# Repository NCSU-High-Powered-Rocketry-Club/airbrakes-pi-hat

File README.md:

# airbrakes-pi-hat

Custom made Pi hat, named "Airbender", for use in Airbrakes

This repository contains the KiCad project files for a Raspberry Pi hat. This Pi hat is meant to control
airbrakes (see the [airbrakes repository](https://github.com/NCSU-High-Powered-Rocketry-Club/AirbrakesV2) for more details on the airbrakes system).

## Features

- Supports from 7V to 20V input voltage, with a maximum amperage of 10A.
- Variable output voltage for the servo power rail (6V to 13V), while simultaneously powering the Pi at 5V.
- Current and voltage sensing for the entire board, which allows measurement of servo load transients.
- Reverse polarity detection and protection on the input power rail
- Reverse polarity detection and protection for the servo cable. Plugging in the cable backwards now will not fry the Raspberry Pi.
- 7 LEDs for monitoring and detecting the health of the board and its interface with the Raspberry Pi.
- Solder jumper pad to select using a servo via PWM or communicate with the servo via UART
- P-MOSFET to disable power to the servo rail when not in use
- Software controlled buzzer for audible alerts

The repository includes schematic symbols, PCB footprints, 3D models, and all board files necessary to review, edit and manufacture the module.

---

## Quick Start — open the project

1. Install KiCad (see [Install and Setup](#install-and-setup) below).
2. Clone the repository:
```bash
git clone https://github.com/NCSU-High-Powered-Rocketry-Club/airbrakes-pi-hat.git && cd airbrakes-pi-hat
```

---

## Install and Setup

First, install KiCad from [kicad.org](https://kicad.org/download/). We recommend using the latest stable release of KiCad for new designs.

### After installation
- Open the `pcb-hat.kicad_pro` project. KiCad will use the `sym-lib-table` and `fp-lib-table` files included here if you open the board/schematic from this checkout.
- If KiCad shows missing library warnings, update the Project Library Tables or use the library manager to add the project's `sym-lib-table` and `fp-lib-table`.

---

## Repository structure

Root-level description (key files/folders):

- `milled_ab_pi_hat/` — folder containing CNC milling files for in-house fabrication at the ECE Makerspace
- `pcb-hat/` — folder which contains the project files for the SMD version of the Pi hat (This is what we order from JLCPCB!)
- `pcb-hat.kicad_sch` — schematic
- `pcb-hat.kicad_pcb` — PCB layout
- `pcb-hat.kicad_pro` — KiCad project file that links schematics, board and library tables
- `sym-lib-table` — project symbol library table that makes project-local symbols available to Eeschema
- `fp-lib-table` — project footprint library table that makes project-local footprints available
- `3dmodels/` — 3D STEP/WRL models used with footprints
- `symbols/` — human-editable symbol libraries (e.g., `connectors.kicad_sym`, `sensors.kicad_sym`)
- `footprints/` — footprint libraries as `.pretty` directories

---

## Library handling

We keep the project-specific libraries inside the repository so that board designs are reproducible and self-contained.

### Symbols
- New symbols are added to the project's `symbols` directory and are registered in the project's `sym-lib-table`.

### Footprints
- Footprints live inside `.pretty` folders in `footprints/`. Add footprints via the footprint editor and store them in an appropriate `footprints/<libname>.pretty` folder.

### 3D models
- 3D models are stored in `3dmodels/` and referenced by footprint model paths. Keep STEP files with good orientation and scale (KiCad's default is mm). We typically download the .step file from the manufacturer's website.
- If you add a footprint that references a 3D model, commit both the footprint in `footprints/` and the 3D model to `3dmodels/`.

---

## Good Practices & Design Rules

- Keep schematic symbols generic and footprints specific: do not hardcode assembly-side changes into symbols.
- Look at the existing schematic to see how we do things and try to be consistent.
- Save new libraries to the project-local tables (not global) to keep designs reproducible.
- Keep PCB footprints accurate — use accurate courtyard, 3D models, and update packaging information.
- Validate with DRC (PCB Editor > Inspect > Design Rules Checker) and ERC (Eeschema > Tools > ERC) before committing changes.
- When collaborating, include notes about part sources (Mouser/Digikey vendor links), footprints used, and any custom pad or thickness changes.

---

## Release & Manufacturing Checklist

Before requesting fab or assembling a board, run this checklist:
1. Run ERC (Eeschema > Tools > ERC) and fix all warnings.
2. Run DRC in PCB Editor and resolve all errors.
3. Create a BOM and confirm manufacturer part numbers and footprints match.
4. Get the [Fabrication Toolkit](https://github.com/bennymeg/Fabrication-Toolkit) plugin from the KiCad plugin repo
5. Click the generate gerber files button in the PCB editor (via the plugin). Keep all default options. Then export it. 
6. Check 3D model alignment in PCB Editor (View > 3D Viewer) to ensure components fit.
7. Tag or branch the repo in Git to preserve the release snapshot.

---

## License

See `LICENSE` at the repo root for licensing details.

---

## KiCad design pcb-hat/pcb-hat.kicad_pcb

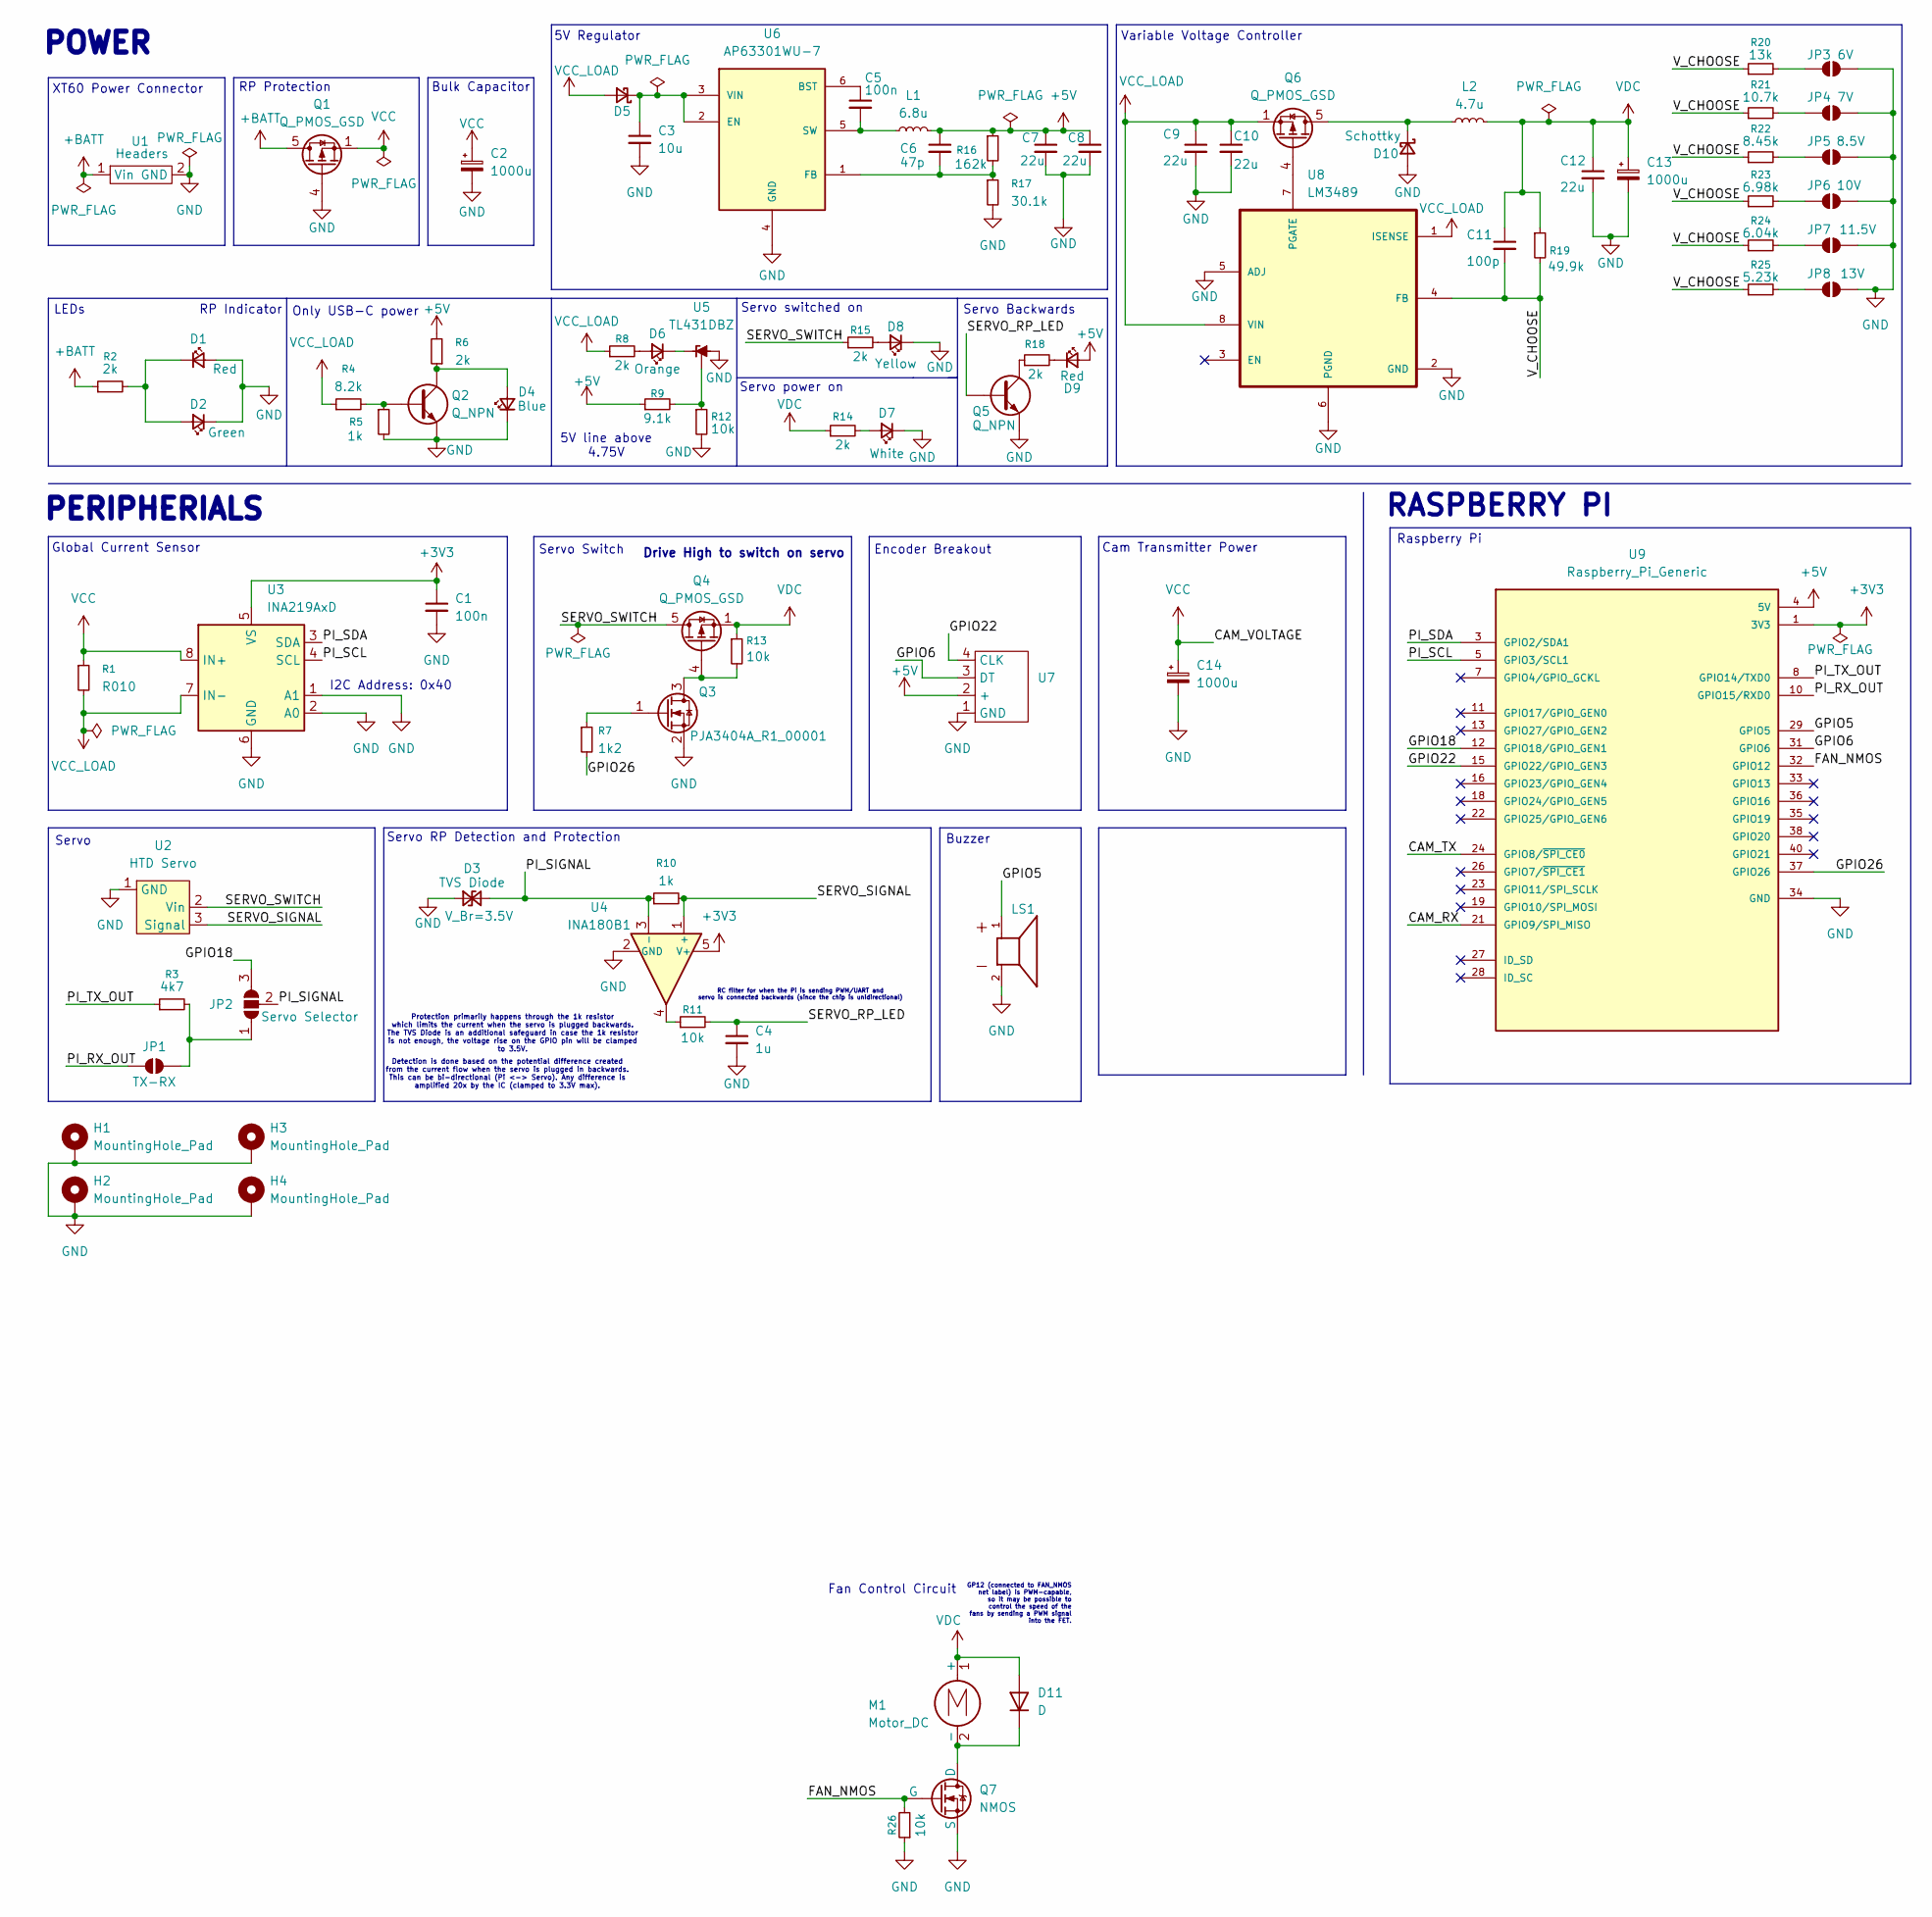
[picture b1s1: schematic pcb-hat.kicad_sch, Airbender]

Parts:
C1, C5: 100n; C_0603_1608Metric_Pad1.08x0.95mm_HandSolder; Digikey PN C0603C104K3RACTU
C2, C13, C14: 1000u; CP_Elec_10x10.5; Digikey PN 399-A783MW108M1ELAS011CT-ND
C3: 10u; C_0603_1608Metric_Pad1.08x0.95mm_HandSolder; Digikey PN 1276-1869-1-ND
C4: 1u; C_0603_1608Metric_Pad1.08x0.95mm_HandSolder; Digikey PN 587-3247-1-ND
C6: 47p; C_0603_1608Metric_Pad1.08x0.95mm_HandSolder; Digikey PN 720-VJ0603A470JXXPW1BCCT-ND
C7, C8, C9, C10, C12: 22u; C_1206_3216Metric; Digikey PN 587-3246-1-ND
C11: 100p; C_0603_1608Metric_Pad1.08x0.95mm_HandSolder; Digikey PN 399-C0603C101J5GACTUCT-ND
D1, D9: LED_Small; LED_0603_1608Metric_Pad1.05x0.95mm_HandSolder; Digikey PN 475-LSQ976.01-N1Q2-1-20-R18CT-ND
D2: LED_Small; LED_0603_1608Metric_Pad1.05x0.95mm_HandSolder; Digikey PN 160-LTST-C190GKTCT-ND
D3: TVS Diode; D_SOD-323F; Digikey PN F6271CT-ND
D4: LED_Small; LED_0603_1608Metric_Pad1.05x0.95mm_HandSolder; Digikey PN 160-1837-1-ND
D5: SS3P4-M3/84A; D_SMP_DO-220AA; Digikey PN SS3P4-M3/84AGICT-ND
D6: LED_Small; LED_0603_1608Metric_Pad1.05x0.95mm_HandSolder; Digikey PN 475-LOQ976.01-P2R2-25-1-20-R18CT-ND
D7: LED_Small; LED_0603_1608Metric_Pad1.05x0.95mm_HandSolder; Digikey PN 350-5992000147FCT-ND
D8: LED_Small; LED_0603_1608Metric_Pad1.05x0.95mm_HandSolder; Digikey PN 160-1437-1-ND
D10: Schottky; D_PowerDI-5; Digikey PN SBR10E45P5-7DICT-ND
D11: D; D_SOD-323_HandSoldering
H1, H2, H3, H4: MountingHole_Pad; MountingHole_2.7mm_M2.5_Pad_TopBottom
JP1: TX to RX?; SolderJumper-2_P1.3mm_Open_RoundedPad1.0x1.5mm
JP2: Servo Selector; SolderJumper-3_P1.3mm_Open_RoundedPad1.0x1.5mm
JP3, JP4, JP5, JP6, JP7, JP8: SolderJumper_2_Open; SolderJumper-2_P1.3mm_Open_RoundedPad1.0x1.5mm
L1: 6.8u; IND_ETQP4M6R8KVK; Digikey PN P19775CT-ND
L2: 4.7u; L_Bourns_SRP1038C_10.0x10.0mm; Digikey PN SRP1038CC-4R7M
LS1: XDCR_SMI-1027-T-5V-R; PARTREV 03/26/2020; Digikey PN smi-1027-t-5v-r
M1: Motor_DC
Q1, Q4, Q6: Q_PMOS_GSD; PJQ4465APAU_R2_000A1; Digikey PN 3757-PJQ4437EP-AU_R2_002A1CT-ND
Q2, Q5: Q_NPN; TSOT-23; Digikey PN MMBT2222A-TP
Q3: PJA3404A_R1_00001; TSOT-23; Digikey PN 3757-PJA3404A_R1_00001CT-ND
Q7: NMOS; SOT-23-3
R1: R010; R_0603_1608Metric_Pad0.98x0.95mm_HandSolder; Digikey PN PE0603FRE570R01Z
R2, R6, R8, R14, R15: 2k; R_0603_1608Metric_Pad0.98x0.95mm_HandSolder; Digikey PN ERJ-PA3J202V
R3: 4k7; R_0603_1608Metric_Pad0.98x0.95mm_HandSolder; Digikey PN RC0603FR-074K7L
R4: 8.2k; R_0603_1608Metric_Pad0.98x0.95mm_HandSolder; Digikey PN 311-8.2KGRCT-ND
R5, R10: 1k; R_0603_1608Metric_Pad0.98x0.95mm_HandSolder; Digikey PN RMCF0603FT1K00CT-ND
R7: 1k2; R_0603_1608Metric_Pad0.98x0.95mm_HandSolder; Digikey PN ERA-3AEB122V
R9: 9.1k; R_0603_1608Metric_Pad0.98x0.95mm_HandSolder; Digikey PN RMCF0603FT9K10CT-ND
R11, R12, R13, R26: 10k; R_0603_1608Metric_Pad0.98x0.95mm_HandSolder; Digikey PN 311-10.0KHRCT-ND
R16: 162k; R_0603_1608Metric_Pad0.98x0.95mm_HandSolder; Digikey PN 541-162KHCT-ND
R17: 30.1k; R_0603_1608Metric_Pad0.98x0.95mm_HandSolder; Digikey PN RMCF0603FT30K1CT-ND
R18: 2k; R_0603_1608Metric_Pad0.98x0.95mm_HandSolder; Digikey PN RMCF0603FT1K00CT-ND
R19: 49.9k; R_0603_1608Metric_Pad0.98x0.95mm_HandSolder; Digikey PN P49.9KDBCT-ND
R20: 13k; R_0603_1608Metric_Pad0.98x0.95mm_HandSolder; Digikey PN 2019-RK73H1JTTD1302FCT-ND
R21: 10.7k; R_0603_1608Metric_Pad0.98x0.95mm_HandSolder; Digikey PN 311-10.7KHRCT-ND
R22: 8.45k; R_0603_1608Metric_Pad0.98x0.95mm_HandSolder; Digikey PN 311-8.45KHRCT-ND
R23: 6.98k; R_0603_1608Metric_Pad0.98x0.95mm_HandSolder; Digikey PN 10-ERA-3AEB6981VCT-ND
R24: 6.04k; R_0603_1608Metric_Pad0.98x0.95mm_HandSolder; Digikey PN 311-6.04KHRCT-ND
R25: 5.23k; R_0603_1608Metric_Pad0.98x0.95mm_HandSolder; Digikey PN 311-5.23KHRCT-ND
U1: Headers; XT60
U2: HTD Servo; Servo
U3: INA219AxD; SOIC-8_3.9x4.9mm_P1.27mm; Digikey PN INA219AIDR
U4: INA180B1; SOT-23-5; Digikey PN 296-47652-1-ND
U5: TL431DBZ; SOT-23; Digikey PN 5399-TL431CT-ND
U6: AP63301WU-7; SOT95P280X100-6N; Digikey PN 31-AP63301WU-7CT-ND
U7: PinHeader_1x04_P2.54mm_Vertical
U8: LM3489; SOP65P490X110-8N; Digikey PN 296-35277-1-ND
U9: Raspberry_Pi_Generic; Pi5Hat

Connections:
+3V3: C1.1, U3.5 (VS), U4.5 (V+), U9.1 (3V3), U9.17 (3V3)
+5V: C6.1, C7.1, C8.1, D9.2 (A), L1.2, R6.2, R9.1, R16.1, U7.2 (+), U9.2 (5V), U9.4 (5V)
+BATT: Q1.5 (D), Q1.6 (D), Q1.7 (D), Q1.8 (D), Q1.9 (D), R2.1, U1.1 (Vin); also elsewhere on the board
/CAM_RX: U9.21 (GPIO9/SPI_MISO); also elsewhere on the board
/CAM_TX: U9.24 (GPIO8/~SPI_CE0); also elsewhere on the board
/FAN_NMOS: Q7.2 (G), R26.2, U9.32 (GPIO12)
/GPIO5: LS1.1, U9.29 (GPIO5)
/GPIO6: U7.3 (DT), U9.31 (GPIO6)
/GPIO18: JP2.3 (B), U9.12 (GPIO18/GPIO_GEN1)
/GPIO22: U7.4 (CLK), U9.15 (GPIO22/GPIO_GEN3)
/GPIO26: R7.2, U9.37 (GPIO26)
/PI_RX_OUT: JP1.1 (A), U9.10 (GPIO15/RXD0)
/PI_SCL: U3.4 (SCL), U9.5 (GPIO3/SCL1)
/PI_SDA: U3.3 (SDA), U9.3 (GPIO2/SDA1)
/PI_SIGNAL: D3.2 (A2), JP2.2 (C), R10.1, U4.3 (-)
/PI_TX_OUT: R3.1, U9.8 (GPIO14/TXD0)
/SERVO_RP_LED: C4.1, Q5.1 (B), R11.2
/SERVO_SIGNAL: R10.2, U2.3 (Signal), U4.1 (+)
/SERVO_SWITCH: Q4.5 (D), Q4.6 (D), Q4.7 (D), Q4.8 (D), Q4.9 (D), R15.1, U2.2 (Vin)
/V_CHOOSE: C11.2, R19.2, R20.1, R21.1, R22.1, R23.1, R24.1, R25.1, U8.4 (FB)
GND: C1.2, C2.2, C3.2, C4.2, C7.2, C8.2, C9.2, C10.2, C12.2, C13.2, C14.2, D1.2 (A), D2.1 (K), D3.1 (A1), D4.1 (K), D7.1 (K), D8.1 (K), D10.2 (A), H1.1 (1_1), H2.1 (1_1), H3.1 (1_1), H4.1 (1_1), JP3.2 (B), JP4.2 (B), JP5.2 (B), JP6.2 (B), JP7.2 (B), JP8.2 (B), LS1.2, Q1.4 (G), Q2.2 (E), Q3.2 (S), Q5.2 (E), Q7.3 (S), R5.2, R12.2, R17.2, R26.1, U1.2 (GND), U2.1 (GND), U3.1 (A1), U3.2 (A0), U3.6 (GND), U4.2 (GND), U5.3 (A), U6.4 (GND), U7.1 (GND), U8.2 (GND), U8.5 (ADJ), U8.6 (PGND), U9.6 (GND), U9.9 (GND), U9.14 (GND), U9.20 (GND), U9.25 (GND), U9.30 (GND), U9.34 (GND), U9.39 (GND); also elsewhere on the board
unnamed: D1.1 (K), D2.2 (A), R2.2
unnamed: D4.2 (A), Q2.3 (C), R6.1
unnamed: C3.1, D5.1 (K), U6.2 (EN), U6.3 (VIN)
unnamed: D6.2 (A), R8.2
unnamed: D6.1 (K), U5.1 (K)
unnamed: D7.2 (A), R14.2
unnamed: D8.2 (A), R15.2
unnamed: D9.1 (K), R18.2
unnamed: D10.1 (K), L2.1, Q6.5 (D), Q6.6 (D), Q6.7 (D), Q6.8 (D), Q6.9 (D)
unnamed 30: D11.1 (K), M1.2 (-), Q7.1 (D); also elsewhere on the board
unnamed: JP1.2 (B), JP2.1 (A), R3.2
unnamed: JP3.1 (A), R20.2
unnamed: JP4.1 (A), R21.2
unnamed: JP5.1 (A), R22.2
unnamed: JP6.1 (A), R23.2
unnamed: JP7.1 (A), R24.2
unnamed: JP8.1 (A), R25.2
unnamed: Q2.1 (B), R4.2, R5.1
unnamed: Q3.3 (D), Q4.4 (G), R13.2
unnamed: Q3.1 (G), R7.1
unnamed: Q5.3 (C), R18.1
unnamed: Q6.4 (G), U8.7 (PGATE)
unnamed: R11.1, U4.4
unnamed: R9.2, R12.1, U5.2 (REF)
unnamed: C5.1, U6.6 (BST)
unnamed: C6.2, R16.2, R17.1, U6.1 (FB)
unnamed: C5.2, L1.1, U6.5 (SW)
VCC: C2.1, C14.1, Q1.1 (S), Q1.2 (S), Q1.3 (S), R1.1, U3.8 (IN+)
VCC_LOAD: C9.1, C10.1, D5.2 (A), Q6.1 (S), Q6.2 (S), Q6.3 (S), R1.2, R4.1, R8.1, U3.7 (IN-), U8.1 (ISENSE), U8.8 (VIN)
VDC: C11.1, C12.1, C13.1, D11.2 (A), L2.2, M1.1 (+), Q4.1 (S), Q4.2 (S), Q4.3 (S), R13.1, R14.1, R19.1

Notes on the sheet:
Global Current Sensor
Buzzer
PERIPHERIALS
Servo RP Detection and Protection
Servo
Encoder Breakout
LEDs
XT60 Power Connector
POWER
I2C Address: 0x40
Drive High to switch on servo
Servo Switch
Protection primarily happens through the 1k resistor which limits the current when the servo is plugged backwards. The TVS Diode is an additional safeguard in case the 1k resistor is not enough, the voltage rise on the GPIO pin will be clamped to 3.5V.
Servo power on
Servo switched on
Detection is done based on the potential difference created from the current flow when the servo is plugged in backwards. This can be bi-directional (Pi <-> Servo). Any difference is amplified 20x by the IC (clamped to 3.3V max).
Only USB-C power
RC filter for when the Pi is sending PWM/UART and servo is connected backwards (since the chip is unidirectional)
Bulk Capacitor
Variable Voltage Controller
RASPBERRY PI
GP12 (connected to FAN_NMOS net label) is PWM-capable, so it may be possible to control the speed of the fans by sending a PWM signal into the FET.
5V line above 4.75V
RP Protection
5V Regulator
Raspberry Pi
Cam Transmitter Power
Fan Control Circuit
Servo Backwards
RP Indicator

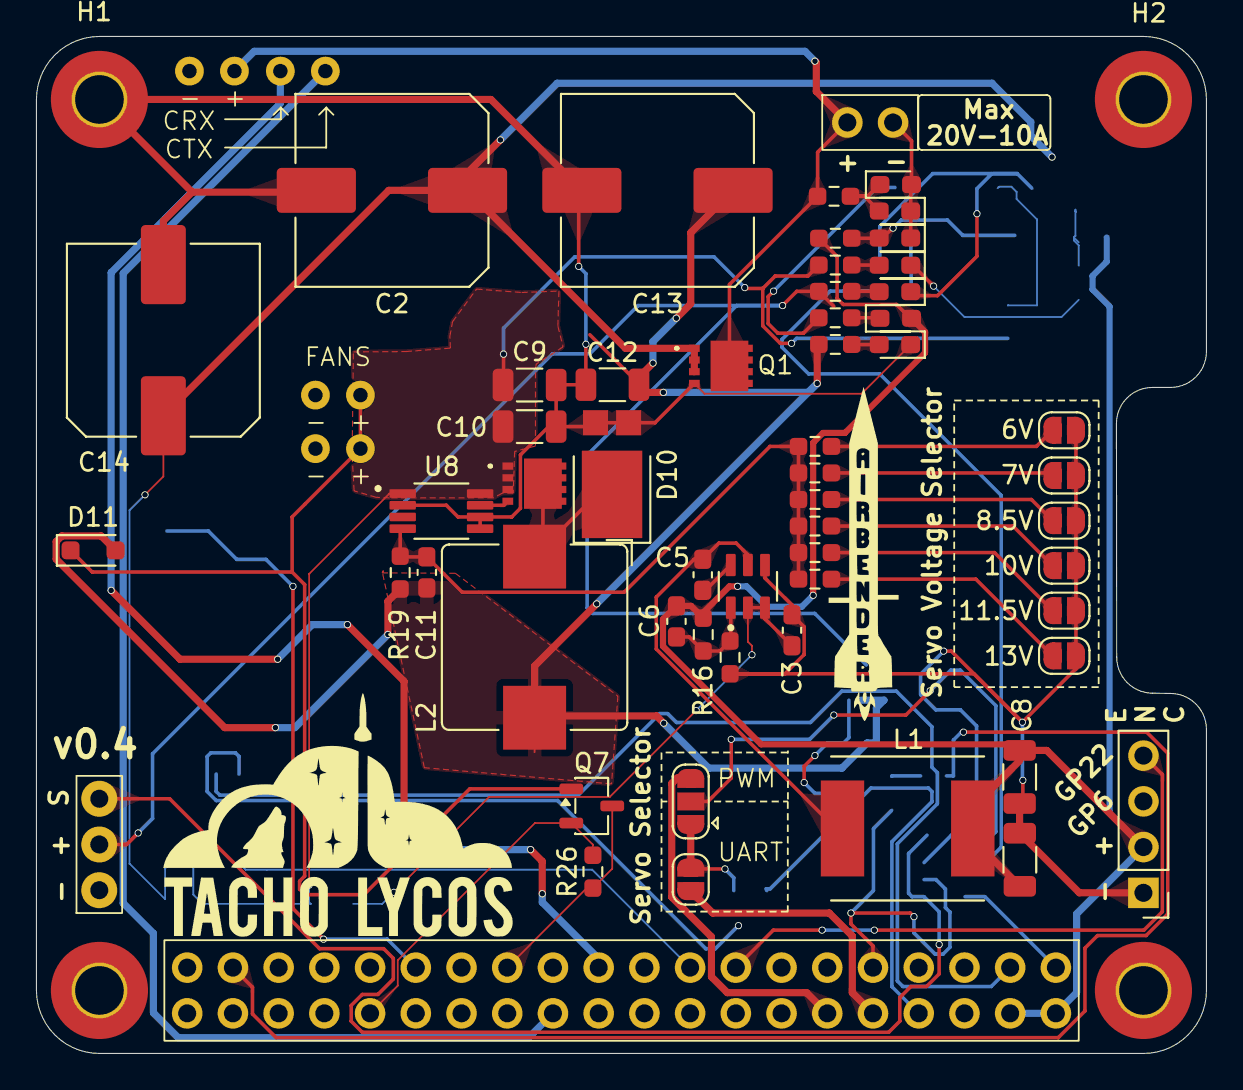
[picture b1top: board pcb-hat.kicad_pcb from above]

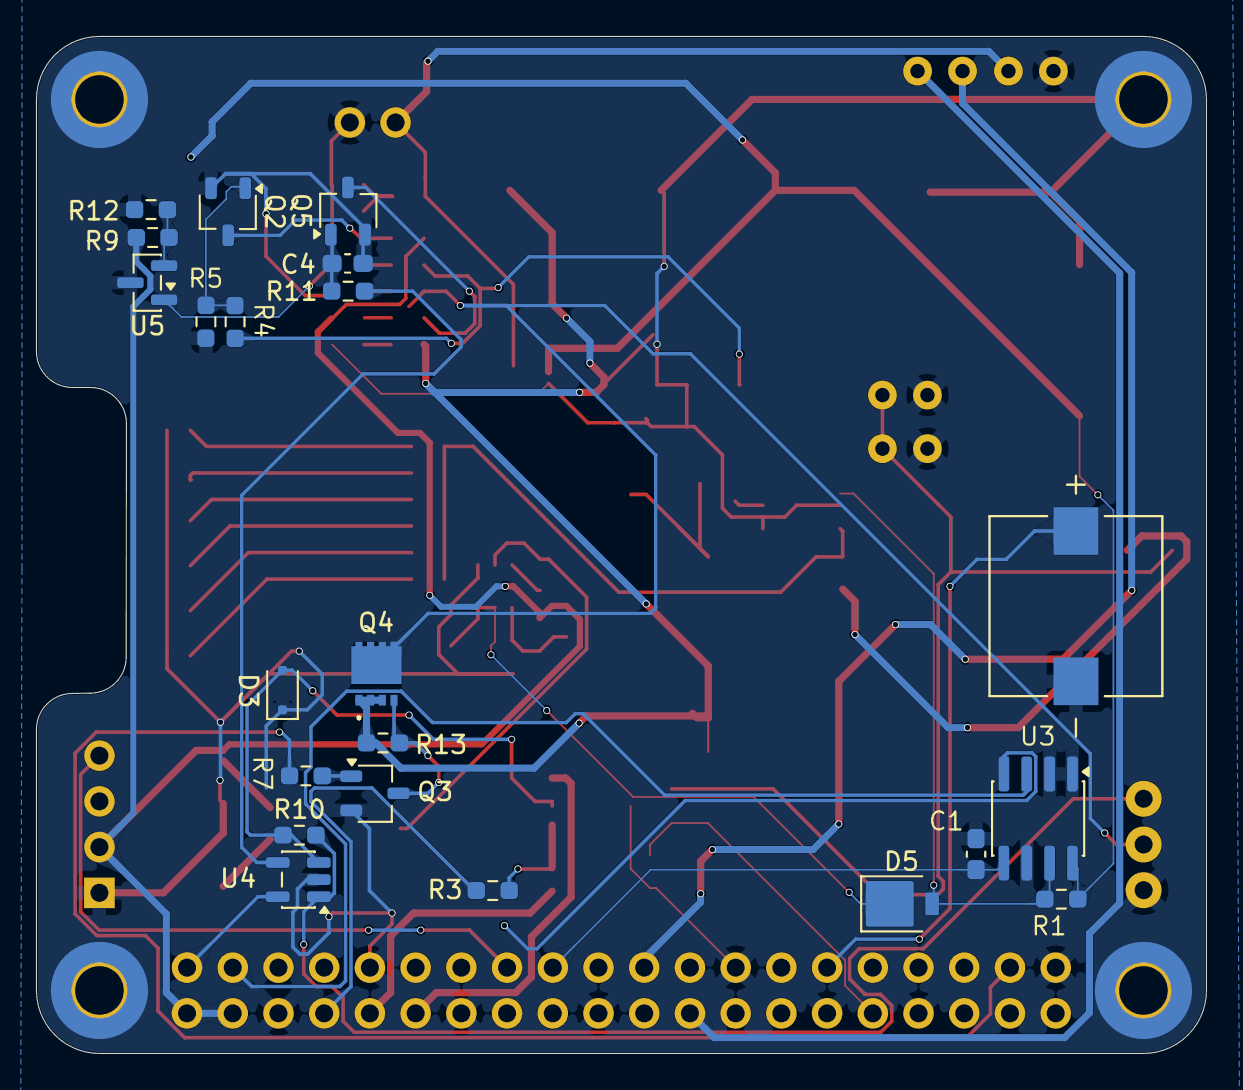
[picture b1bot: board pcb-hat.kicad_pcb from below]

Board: 4 copper layers, 65.0 x 56.5 mm, 86 parts (22 on the bottom side), 51 nets.

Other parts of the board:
FAN: Fan Connection; Fan Connector
FAN#2: Fan Connection; Fan Connector
FANS: Fan Connection; Fan Connector
RPi5: RPi5; Raspberry Pi 5

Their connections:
+BATT: FAN.2; also elsewhere on the board
/CAM_RX: FAN.3; also elsewhere on the board
/CAM_TX: FAN.4; also elsewhere on the board
GND: FAN.1, FAN#2.1, FANS.1; also elsewhere on the board
unnamed 30: FAN#2.2, FANS.2; also elsewhere on the board

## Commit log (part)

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2025-11-03 Add old AB pi hat
2025-11-05 Add pcb hat directory
2025-11-05 added SMD buzzer and current sensor
2025-11-06 Finish current sensor & buzzer wiring
2025-11-08 5V Converter sym/footprint and variable regulator sym/footprint/3dmodule added to files
2025-11-09 Almost finish main voltage regulator
    only pot is left
2025-11-10 Rearrange stuff
2025-11-10 Added solder jumps and resistors
2025-11-11 Resistance values and Decoupling capacitor added
2025-11-11 LED added
2025-11-12 Add Pi, LED, Servo to the schematic
2025-11-12 Add new 5V regulator part, finish Servo connection
    Also fix footprint of 7, 8, and 9V resistors to 0603 hand soldered
2025-11-12 oop forgot to add the new step and footprint files
2025-11-12 Update pcb-hat.kicad_sch
    replaced 5v regulator
2025-11-12 Update PiHatComponents.kicad_sym
    horizontal breakouts
2025-11-12 Update PiHatComponents.kicad_sym
    vertical breakouts
2025-11-14 WIP: Add breakouts to schematic
2025-11-14 symbol/footprint/connections for PiHeaders/pinouts
2025-11-15 pi breakout symbol changes
2025-11-17 Don't short pwr to gnd for current sensor
    Also use higher power rating for shunt
2025-11-18 Add mosfets, new led, and cleanup schematic some more
2025-11-18 TODO: Add gate resistors on mosfets
2025-11-19 Create horizontal_breakout_footprint.kicad_mod
    horizontal breakout footprint
2025-11-19 Switch out the 5V regulator
2025-11-20 Cleanup: Add pwr_flags, reference designators, delete old 5v regulator from symbol library
2025-11-23 Add fuse for servo
    Also update footprints with their corresponding 3d models, and start adding Net classes. Delete old 5v linear voltage regulator footprint
2025-11-23 Add PMOS for RP protection
2025-11-23 Make some more space in sch
2025-11-24 Finish LED circuitry
    Involves anti parallel LEDs and a NPN Transistor to control voltage received on the blue led
2025-12-03 More net classes, fix 2 major bugs with current sensor wiring
2025-12-04 Finish Schematic
    Add a switch and combine the 2 servos into one
2025-12-04 Add a readme
2025-12-04 Add 3d model for the switch
2025-12-20 Define edge cuts, JLCPCB board settings
2025-12-22 WIP: Fix footprints, add new jumper pad, 3d models. Begin routing
2025-12-27 Finish PCB design v0.1
2025-12-27 Update README, add pictures
2026-01-11 Fix blue LED not turning on
2026-01-11 Change digikey PN for resistors
2026-01-18 Update schematic and reroute PCB
    See the github PR for all changes
2026-01-18 Use AP63301 instead of AP63300 for lower voltage ripple during transients
2026-01-18 Add silkscreen for encoder and buzzer
2026-01-21 Revert back to using 3.3V and no flyback for buzzer
2026-01-21 Add gnd pour on B.Cu, change default trace thickness to 0.2mm
    Also make the SW node to the inductor slightly closer
2026-01-21 Make thermal vias untented, add some reference desigs back
2026-01-21 Add note about cap
2026-01-25 Add digikey pn's to caps and resistors, order board
2026-03-07 WIP: Using new pmos, voltage controller
    Removed fuse, added 7th LED, added servo RP detection and protection (pending testing)
2026-03-09 More work on schematic
2026-03-10 Fix servo RP detection circuit
    Start work on routing
2026-03-13 Finish routing PCB
2026-03-22 Save files with KiCAD v10
2026-03-25 Update feature list in README
    Updated set of features which wasn't updated since Airbender v0.1.
